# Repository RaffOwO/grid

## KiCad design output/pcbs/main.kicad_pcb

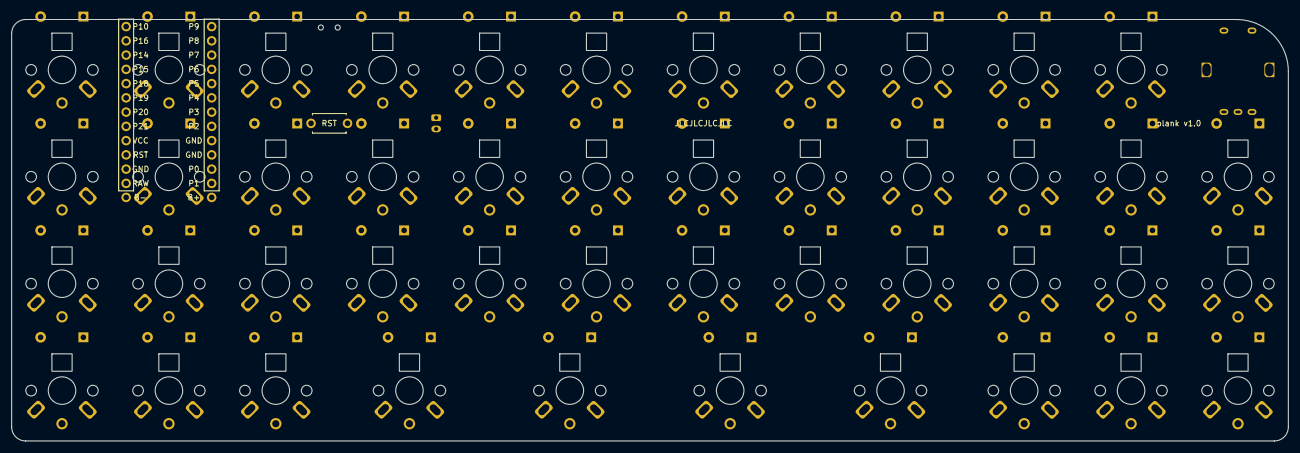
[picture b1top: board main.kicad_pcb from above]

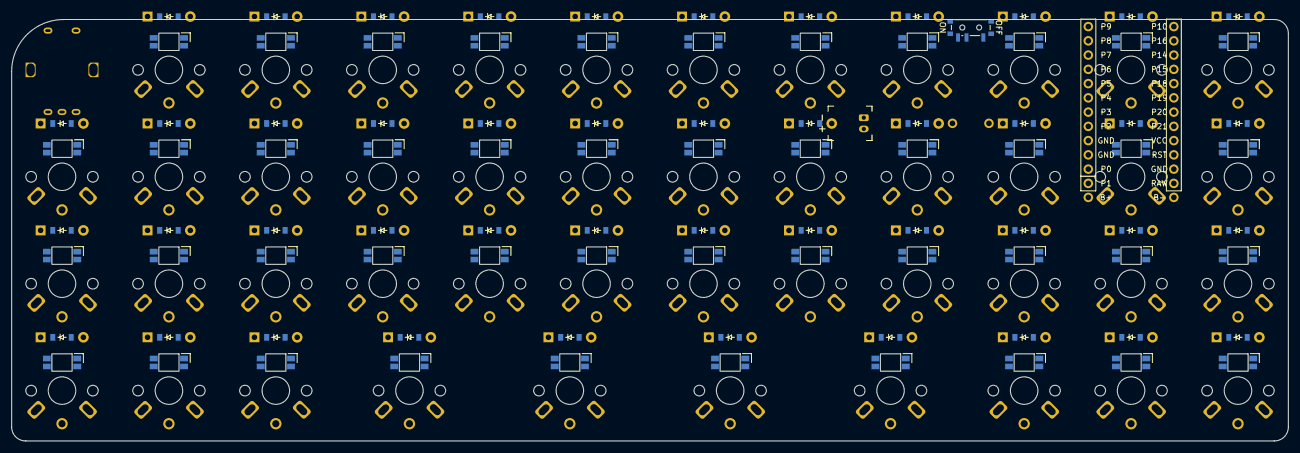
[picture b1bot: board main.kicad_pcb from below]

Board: 2 copper layers, 227.5 x 75.1 mm, 140 parts (92 on the bottom side), 111 nets, no tracks yet.

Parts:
D1, D2, D3, D4, D5, D6, D7, D8, D9, D10, D11, D12, D13, D14, D15, D16, D17, D18, D19, D20, D21, D22, D23, D24, D25, D26, D27, D28, D29, D30, D31, D32, D33, D34, D35, D36, D37, D38, D39, D40, D41, D42, D43, D44, D45: diode_tht_sod123
JST1: battery_connector_jst_ph_2
LED1, LED2, LED3, LED4, LED5, LED6, LED7, LED8, LED9, LED10, LED11, LED12, LED13, LED14, LED15, LED16, LED17, LED18, LED19, LED20, LED21, LED22, LED23, LED24, LED25, LED26, LED27, LED28, LED29, LED30, LED31, LED32, LED33, LED34, LED35, LED36, LED37, LED38, LED39, LED40, LED41, LED42, LED43, LED44, LED45: led_SK6812mini-e (per-keysingle-side)
MCU1: MCU_NRF52840
PWR1: power_switch_smd_side
RE1: rotary_encoder_ec11_ec12
RST1: reset_switch_tht_top
S1, S2, S3, S4, S5, S6, S7, S8, S9, S10, S11, S12, S13, S14, S15, S16, S17, S18, S19, S20, S21, S22, S23, S24, S25, S26, S27, S28, S29, S30, S31, S32, S33, S34, S35, S36, S37, S38, S39, S40, S41, S42, S43, S44, S45: Choc+Jerzii

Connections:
BAT_P: JST1.2, PWR1.2
GND: JST1.1, LED1.3, LED2.3, LED3.3, LED4.3, LED5.3, LED6.3, LED7.3, LED8.3, LED9.3, LED10.3, LED11.3, LED12.3, LED13.3, LED14.3, LED15.3, LED16.3, LED17.3, LED18.3, LED19.3, LED20.3, LED21.3, LED22.3, LED23.3, LED24.3, LED25.3, LED26.3, LED27.3, LED28.3, LED29.3, LED30.3, LED31.3, LED32.3, LED33.3, LED34.3, LED35.3, LED36.3, LED37.3, LED38.3, LED39.3, LED40.3, LED41.3, LED42.3, LED43.3, LED44.3, LED45.3, MCU1.3, MCU1.4, MCU1.23, RE1.C, RST1.1
LED_1: LED3.4, LED4.2
LED_2: LED2.4, LED3.2
LED_3: LED1.4, LED2.2
LED_4: LED1.2, LED5.4
LED_5: LED5.2, LED6.4
LED_6: LED6.2, LED7.4
LED_7: LED7.2, LED8.4
LED_8: LED8.2, LED12.4
LED_9: LED11.4, LED12.2
LED_10: LED10.4, LED11.2
LED_11: LED9.4, LED10.2
LED_12: LED9.2, LED13.4
LED_13: LED13.2, LED14.4
LED_14: LED14.2, LED15.4
LED_15: LED15.2, LED16.4
LED_16: LED16.2, LED20.4
LED_17: LED19.4, LED20.2
LED_18: LED18.4, LED19.2
LED_19: LED17.4, LED18.2
LED_20: LED17.2, LED21.4
LED_21: LED21.2, LED22.4
LED_22: LED22.2, LED23.4
LED_23: LED23.2, LED26.4
LED_24: LED25.4, LED26.2
LED_25: LED24.4, LED25.2
LED_26: LED24.2, LED27.4
LED_27: LED27.2, LED28.4
LED_28: LED28.2, LED29.4
LED_29: LED29.2, LED30.4
LED_30: LED30.2, LED34.4
LED_31: LED33.4, LED34.2
LED_32: LED32.4, LED33.2
LED_33: LED31.4, LED32.2
LED_34: LED31.2, LED35.4
LED_35: LED35.2, LED36.4
LED_36: LED36.2, LED37.4
LED_37: LED37.2, LED38.4
LED_38: LED38.2, LED42.4
LED_39: LED41.4, LED42.2
LED_40: LED40.4, LED41.2
LED_41: LED39.4, LED40.2
LED_42: LED39.2, LED43.4
LED_43: LED43.2, LED44.4
LED_44: LED44.2, LED45.4
P0: MCU1.2, S5.1, S6.1, S7.1, S8.1
P1: MCU1.1, S1.1, S2.1, S3.1, S4.1
P2: MCU1.5, S17.1, S18.1, S19.1, S20.1
P3: MCU1.6, S21.1, S22.1, S23.1
P4: MCU1.7, S24.1, S25.1, S26.1
P5: MCU1.8, S27.1, S28.1, S29.1, S30.1
P6: MCU1.9, S31.1, S32.1, S33.1, S34.1
P7: MCU1.10, S35.1, S36.1, S37.1, S38.1
P8: MCU1.11, S39.1, S40.1, S41.1, S42.1
P9: MCU1.12, S43.1, S44.1, S45.1
P10: MCU1.13, RE1.S1
P14: MCU1.15, S9.1, S10.1, S11.1, S12.1
P15: D2.1, D6.1, D10.1, D14.1, D18.1, D21.1, D24.1, D28.1, D32.1, D36.1, D40.1, D44.1, MCU1.16
P18: D1.1, D5.1, D9.1, D13.1, D17.1, D27.1, D31.1, D35.1, D39.1, D43.1, MCU1.17
P19: D4.1, D8.1, D12.1, D16.1, D20.1, D23.1, D26.1, D30.1, D34.1, D38.1, D42.1, MCU1.18
P20: MCU1.19, S13.1, S14.1, S15.1, S16.1
P21: D3.1, D7.1, D11.1, D15.1, D19.1, D22.1, D25.1, D29.1, D33.1, D37.1, D41.1, D45.1, MCU1.20
RAW: MCU1.24, PWR1.3
RST: MCU1.22, RST1.2
VCC: LED1.1, LED2.1, LED3.1, LED4.1, LED5.1, LED6.1, LED7.1, LED8.1, LED9.1, LED10.1, LED11.1, LED12.1, LED13.1, LED14.1, LED15.1, LED16.1, LED17.1, LED18.1, LED19.1, LED20.1, LED21.1, LED22.1, LED23.1, LED24.1, LED25.1, LED26.1, LED27.1, LED28.1, LED29.1, LED30.1, LED31.1, LED32.1, LED33.1, LED34.1, LED35.1, LED36.1, LED37.1, LED38.1, LED39.1, LED40.1, LED41.1, LED42.1, LED43.1, LED44.1, LED45.1, MCU1.21
eight_bottom: D28.2, S28.2
eight_home: D29.2, S29.2
eight_mod: D27.2, S27.2
eight_top: D30.2, S30.2
eleven_bottom: D40.2, S40.2
eleven_home: D41.2, S41.2
eleven_mod: D39.2, S39.2
eleven_top: D42.2, S42.2
five_bottom: D18.2, S18.2
five_home: D19.2, S19.2
five_mod: D17.2, S17.2
five_top: D20.2, S20.2
four_bottom: D14.2, S14.2
four_home: D15.2, S15.2
four_mod: D13.2, S13.2
four_top: D16.2, S16.2
nine_bottom: D32.2, S32.2
nine_home: D33.2, S33.2
nine_mod: D31.2, S31.2
nine_top: D34.2, S34.2
one_bottom: D2.2, S2.2
one_home: D3.2, S3.2
one_mod: D1.2, S1.2
one_top: D4.2, S4.2
seven_bottom: D24.2, S24.2
seven_home: D25.2, S25.2
seven_top: D26.2, S26.2
six_bottom: D21.2, S21.2
six_home: D22.2, S22.2
six_top: D23.2, S23.2
ten_bottom: D36.2, S36.2
ten_home: D37.2, S37.2
ten_mod: D35.2, S35.2
ten_top: D38.2, S38.2
three_bottom: D10.2, S10.2
three_home: D11.2, S11.2
three_mod: D9.2, S9.2
three_top: D12.2, S12.2
twelve_bottom: D44.2, S44.2
twelve_home: D45.2, S45.2
twelve_mod: D43.2, S43.2
two_bottom: D6.2, S6.2
two_home: D7.2, S7.2
two_mod: D5.2, S5.2
two_top: D8.2, S8.2
